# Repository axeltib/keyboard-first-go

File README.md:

# My first keyboard project

## Introduction

## Where to find stuff

# Some good resource

- For generating keboard layouts http://www.keyboard-layout-editor.com/#/
- For generating cad files from layout http://builder.swillkb.com/

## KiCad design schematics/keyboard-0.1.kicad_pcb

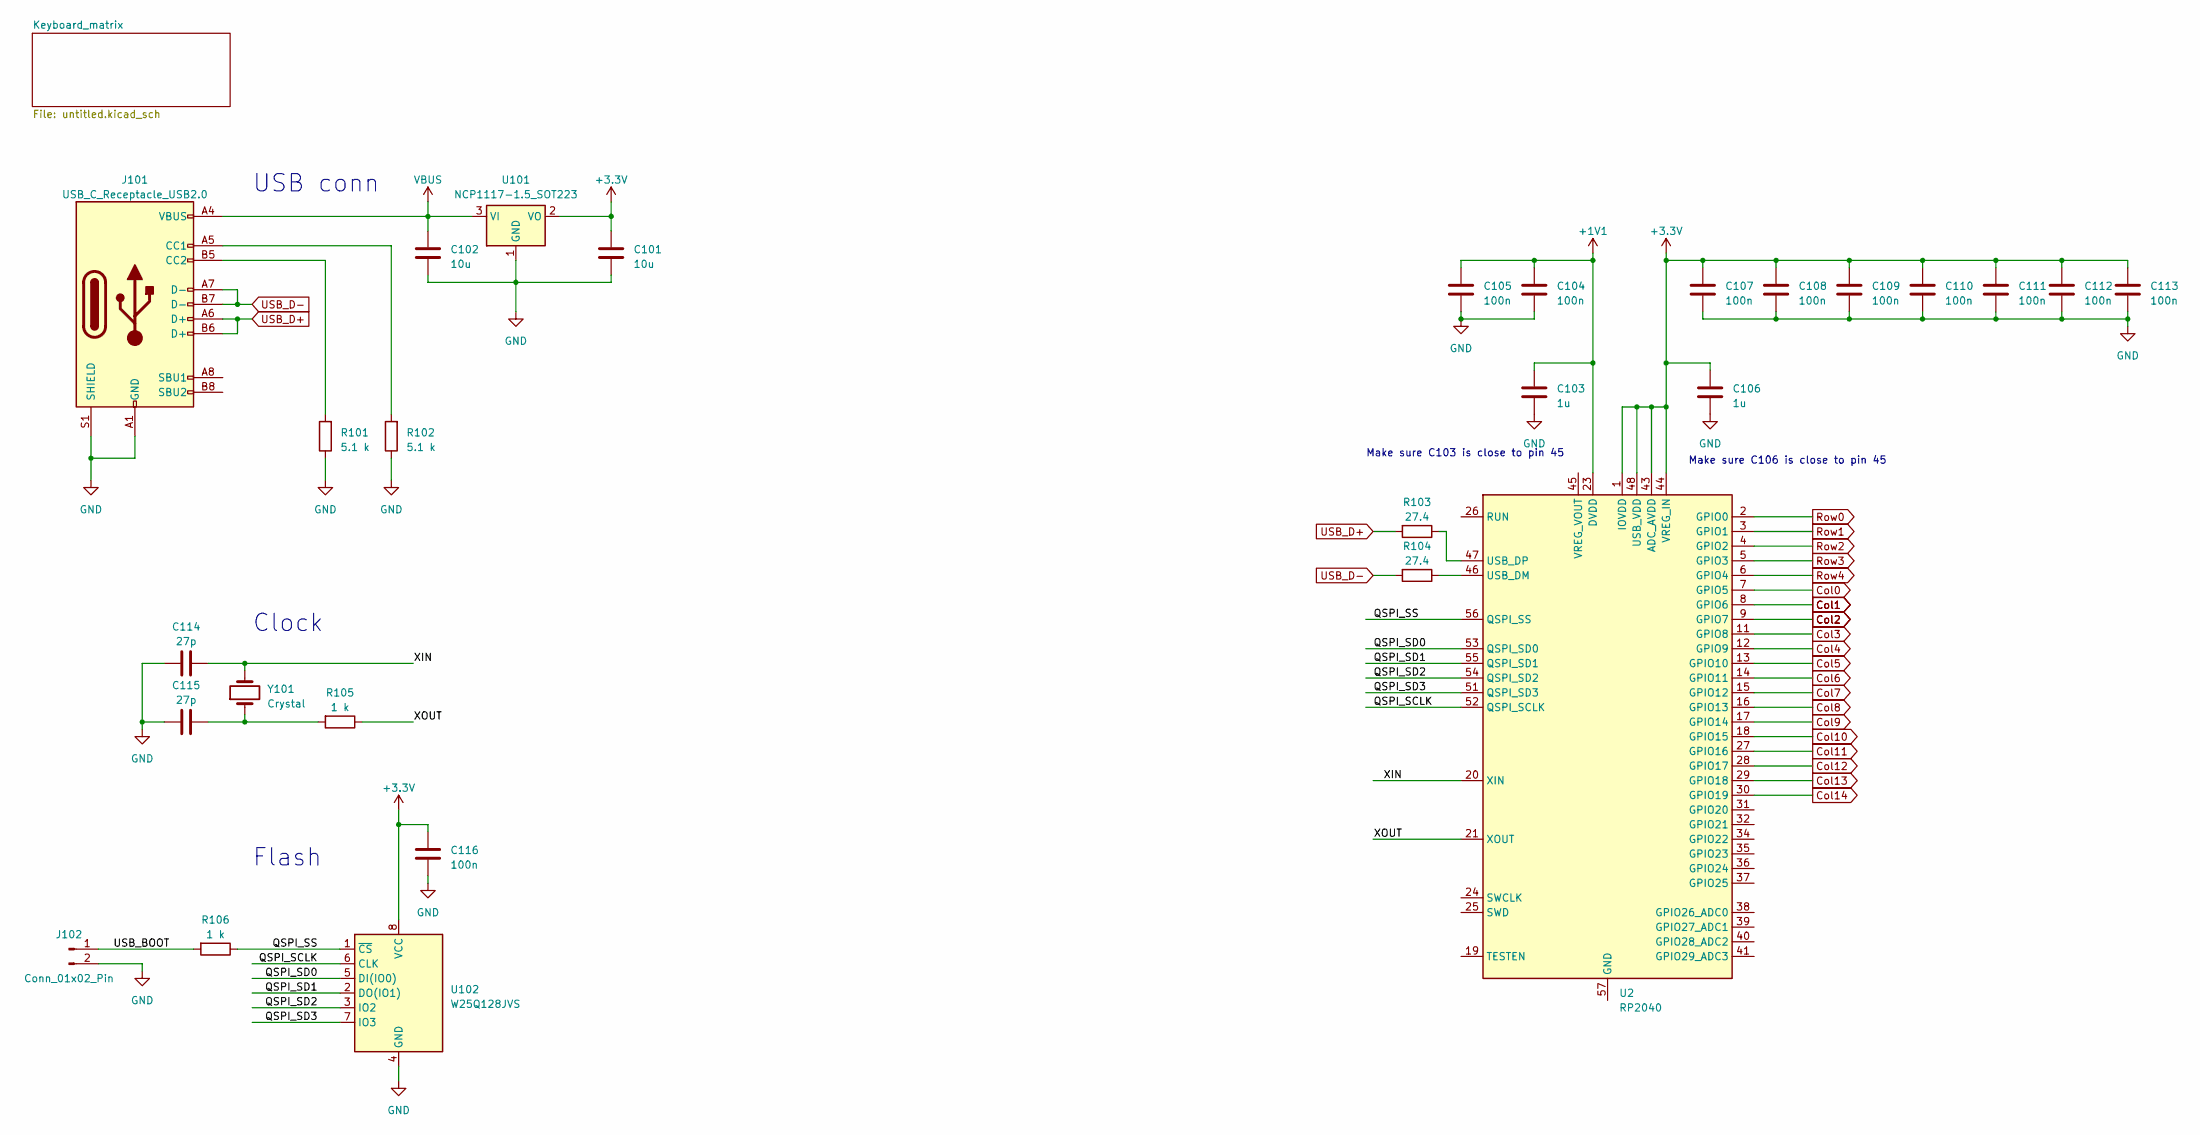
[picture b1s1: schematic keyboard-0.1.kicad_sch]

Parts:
C101, C102: 10u; C_0201_0603Metric
C103, C106: 1u; C_0201_0603Metric
C104, C105, C107, C108, C109, C110, C111, C112, C113, C116: 100n; C_0201_0603Metric
C114, C115: 27p; C_0201_0603Metric
J101: USB_C_Receptacle_USB2.0; USB_C_Receptacle_Amphenol_12401548E4-2A
J102: Conn_01x02_Pin; R_0805_2012Metric_Pad1.20x1.40mm_HandSolder
R101, R102: 5.1 k; R_0201_0603Metric
R103, R104: 27.4; R_0201_0603Metric
R105, R106: 1 k; R_0201_0603Metric
U2: RP2040; QFN-56-1EP_7x7mm_P0.4mm_EP3.2x3.2mm
U101: NCP1117-1.5_SOT223; SOT-223-3_TabPin2
U102: W25Q128JVS; SOIC-8_5.23x5.23mm_P1.27mm
Y101: Crystal; Crystal_SMD_0603-2Pin_6.0x3.5mm

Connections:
+1V1: C103.1, C104.1, C105.1, U2.23 (DVDD), U2.50 (DVDD)
+3.3V: C101.1, C106.1, C107.1, C108.1, C109.1, C110.1, C111.1, C112.1, C113.1, C116.1, U2.1 (IOVDD), U2.10 (IOVDD), U2.22 (IOVDD), U2.33 (IOVDD), U2.42 (IOVDD), U2.43 (ADC_AVDD), U2.44 (VREG_IN), U2.48 (USB_VDD), U2.49 (IOVDD), U101.2 (VO), U102.8 (VCC)
/QSPI_SCLK: U2.52 (QSPI_SCLK), U102.6 (CLK)
/QSPI_SD0: U2.53 (QSPI_SD0), U102.5 (DI(IO0))
/QSPI_SD1: U2.55 (QSPI_SD1), U102.2 (DO(IO1))
/QSPI_SD2: U2.54 (QSPI_SD2), U102.3 (IO2)
/QSPI_SD3: U2.51 (QSPI_SD3), U102.7 (IO3)
/QSPI_SS: R106.1, U2.56 (QSPI_SS), U102.1 (~CS)
/USB_BOOT: J102.1, R106.2
/XIN: C114.2, U2.20 (XIN), Y101.2
/XOUT: R105.1, U2.21 (XOUT)
Col0: U2.7 (GPIO5); also elsewhere on the board
Col1: U2.8 (GPIO6); also elsewhere on the board
Col2: U2.9 (GPIO7); also elsewhere on the board
Col3: U2.11 (GPIO8); also elsewhere on the board
Col4: U2.12 (GPIO9); also elsewhere on the board
Col5: U2.13 (GPIO10); also elsewhere on the board
Col6: U2.14 (GPIO11); also elsewhere on the board
Col7: U2.15 (GPIO12); also elsewhere on the board
Col8: U2.16 (GPIO13); also elsewhere on the board
Col9: U2.17 (GPIO14); also elsewhere on the board
Col10: U2.18 (GPIO15); also elsewhere on the board
Col11: U2.27 (GPIO16); also elsewhere on the board
Col12: U2.28 (GPIO17); also elsewhere on the board
Col13: U2.29 (GPIO18); also elsewhere on the board
Col14: U2.30 (GPIO19)
GND: C101.2, C102.2, C103.2, C104.2, C105.2, C106.2, C107.2, C108.2, C109.2, C110.2, C111.2, C112.2, C113.2, C114.1, C115.1, C116.2, J101.A1 (GND), J101.A12 (GND), J101.B1 (GND), J101.B12 (GND), J101.S1 (SHIELD), J102.2, R101.1, R102.1, U101.1 (GND), U102.4 (GND)
unnamed: C115.2, R105.2, Y101.1
unnamed: J101.A5 (CC1), R102.2
unnamed: J101.B5 (CC2), R101.2
unnamed: R104.1, U2.46 (USB_DM)
unnamed: R103.1, U2.47 (USB_DP)
Row0: U2.2 (GPIO0); also elsewhere on the board
Row1: U2.3 (GPIO1); also elsewhere on the board
Row2: U2.4 (GPIO2); also elsewhere on the board
Row3: U2.5 (GPIO3); also elsewhere on the board
Row4: U2.6 (GPIO4); also elsewhere on the board
USB_D+: J101.A6 (D+), J101.B6 (D+), R103.2
USB_D-: J101.A7 (D-), J101.B7 (D-), R104.2
VBUS: C102.1, J101.A4 (VBUS), J101.A9 (VBUS), J101.B4 (VBUS), J101.B9 (VBUS), U101.3 (VI)

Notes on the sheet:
USB conn
Clock
Make sure C106 is close to pin 45
Flash
Make sure C103 is close to pin 45

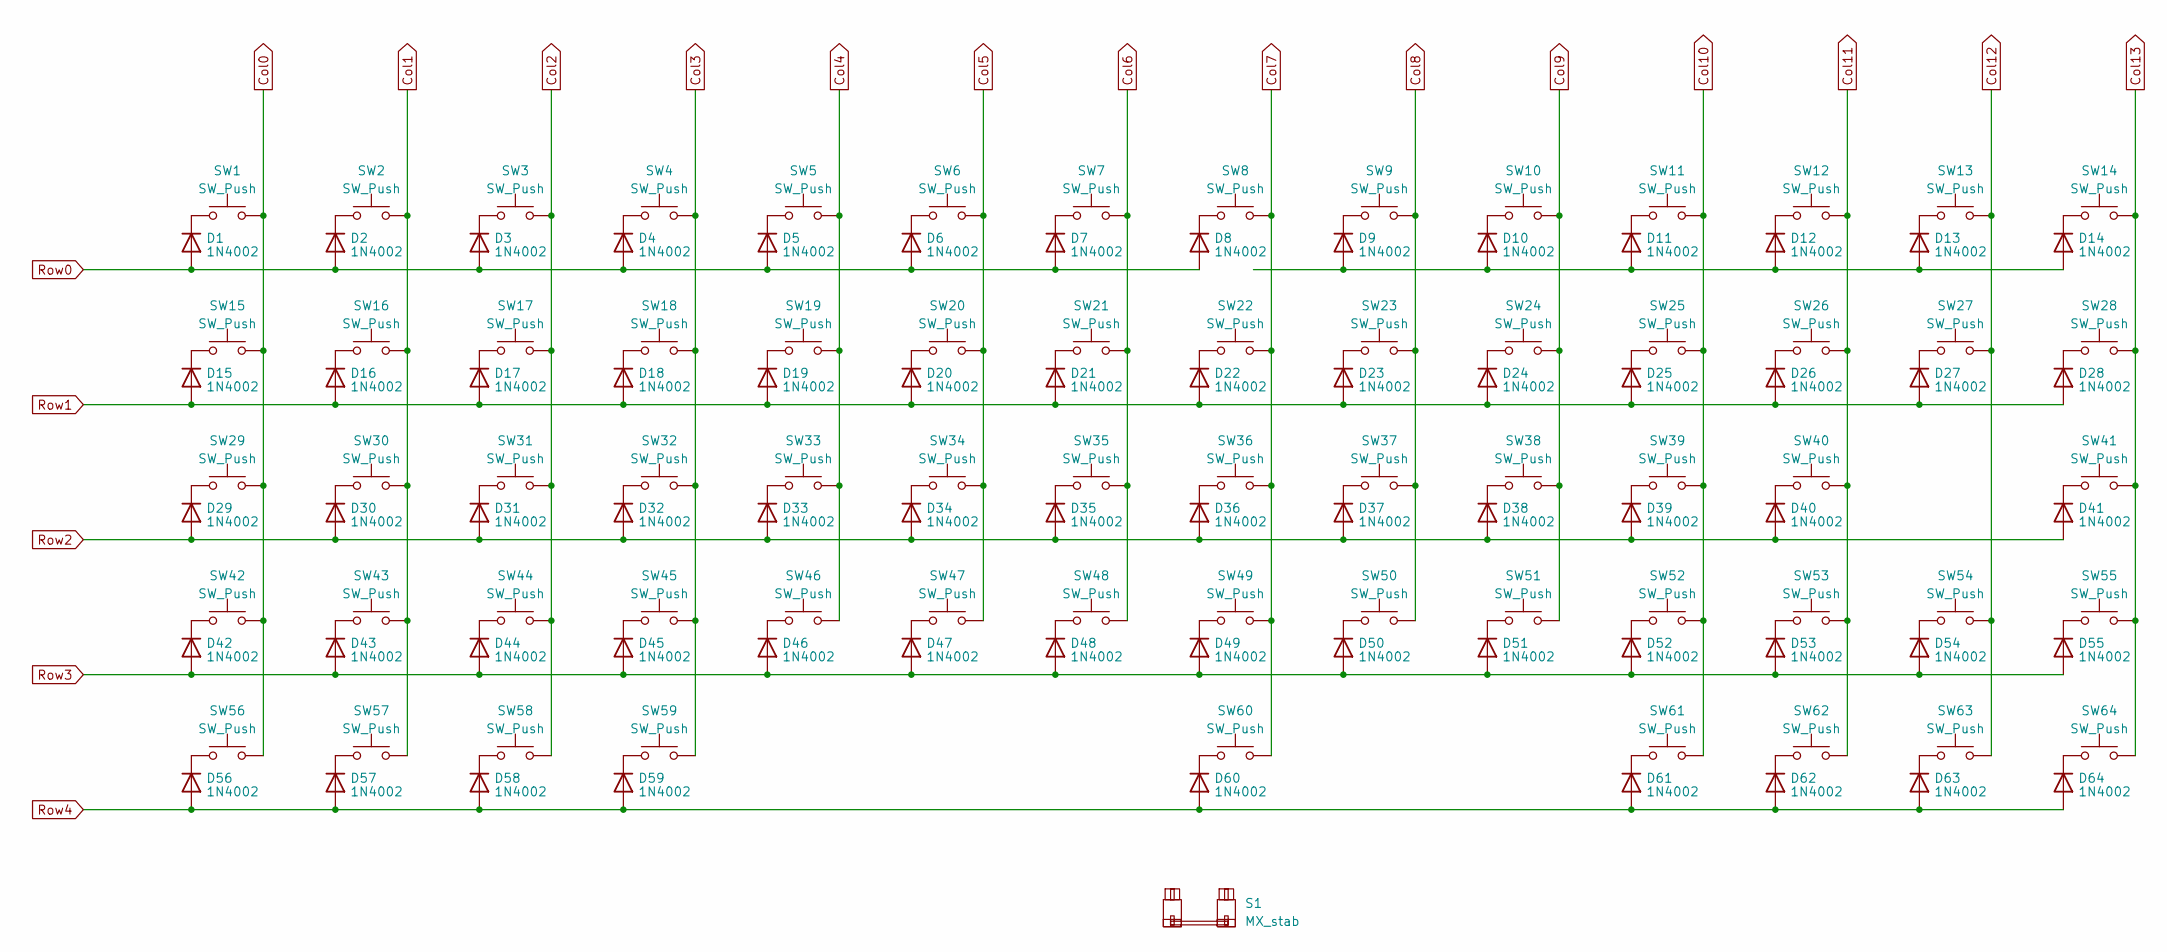
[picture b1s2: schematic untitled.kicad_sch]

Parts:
D1, D2, D3, D4, D5, D6, D7, D8, D9, D10, D11, D12, D13, D14, D15, D16, D17, D18, D19, D20, D21, D22, D23, D24, D25, D26, D27, D28, D29, D30, D31, D32, D33, D34, D35, D36, D37, D38, D39, D40, D41, D42, D43, D44, D45, D46, D47, D48, D49, D50, D51, D52, D53, D54, D55, D56, D57, D58, D59, D60, D61, D62, D63, D64: 1N4002; D_SOD-123
S1: MX_stab; STAB_MX_P_6u
SW1, SW2, SW3, SW4, SW5, SW6, SW7, SW8, SW9, SW10, SW11, SW12, SW13, SW16, SW17, SW18, SW19, SW20, SW21, SW22, SW23, SW24, SW25, SW26, SW27, SW28, SW30, SW31, SW32, SW33, SW34, SW35, SW36, SW37, SW38, SW39, SW40, SW43, SW44, SW45, SW46, SW47, SW48, SW49, SW50, SW51, SW52, SW53, SW54, SW55, SW57, SW58, SW59, SW60, SW62, SW63, SW64: SW_Push; SW_MX_1u
SW14, SW15, SW42: SW_Push; SW_MX_1.5u
SW29, SW41: SW_Push; SW_MX_1.75u
SW56, SW61: SW_Push; SW_MX_1.25u

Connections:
Col0: SW1.2, SW15.2, SW29.2, SW42.2, SW56.2; also elsewhere on the board
Col1: SW2.2, SW16.2, SW30.2, SW43.2, SW57.2; also elsewhere on the board
Col2: SW3.2, SW17.2, SW31.2, SW44.2, SW58.2; also elsewhere on the board
Col3: SW4.2, SW18.2, SW32.2, SW45.2, SW59.2; also elsewhere on the board
Col4: SW5.2, SW19.2, SW33.2, SW46.2; also elsewhere on the board
Col5: SW6.2, SW20.2, SW34.2, SW47.2; also elsewhere on the board
Col6: SW7.2, SW21.2, SW35.2, SW48.2; also elsewhere on the board
Col7: SW8.2, SW22.2, SW36.2, SW49.2, SW60.2; also elsewhere on the board
Col8: SW9.2, SW23.2, SW37.2, SW50.2; also elsewhere on the board
Col9: SW10.2, SW24.2, SW38.2, SW51.2; also elsewhere on the board
Col10: SW11.2, SW25.2, SW39.2, SW52.2, SW61.2; also elsewhere on the board
Col11: SW12.2, SW26.2, SW40.2, SW53.2, SW62.2; also elsewhere on the board
Col12: SW13.2, SW27.2, SW54.2, SW63.2; also elsewhere on the board
Col13: SW14.2, SW28.2, SW41.2, SW55.2, SW64.2; also elsewhere on the board
unnamed: D1.1 (K), SW1.1
unnamed: D2.1 (K), SW2.1
unnamed: D3.1 (K), SW3.1
unnamed: D4.1 (K), SW4.1
unnamed: D5.1 (K), SW5.1
unnamed: D6.1 (K), SW6.1
unnamed: D7.1 (K), SW7.1
unnamed: D8.1 (K), SW8.1
unnamed: D9.1 (K), SW9.1
unnamed: D9.2 (A), D10.2 (A), D11.2 (A), D12.2 (A), D13.2 (A), D14.2 (A)
unnamed: D10.1 (K), SW10.1
unnamed: D11.1 (K), SW11.1
unnamed: D12.1 (K), SW12.1
unnamed: D13.1 (K), SW13.1
unnamed: D14.1 (K), SW14.1
unnamed: D15.1 (K), SW15.1
unnamed: D16.1 (K), SW16.1
unnamed: D17.1 (K), SW17.1
unnamed: D18.1 (K), SW18.1
unnamed: D19.1 (K), SW19.1
unnamed: D20.1 (K), SW20.1
unnamed: D21.1 (K), SW21.1
unnamed: D22.1 (K), SW22.1
unnamed: D23.1 (K), SW23.1
unnamed: D24.1 (K), SW24.1
unnamed: D25.1 (K), SW25.1
unnamed: D26.1 (K), SW26.1
unnamed: D27.1 (K), SW27.1
unnamed: D28.1 (K), SW28.1
unnamed: D29.1 (K), SW29.1
unnamed: D30.1 (K), SW30.1
unnamed: D31.1 (K), SW31.1
unnamed: D32.1 (K), SW32.1
unnamed: D33.1 (K), SW33.1
unnamed: D34.1 (K), SW34.1
unnamed: D35.1 (K), SW35.1
unnamed: D36.1 (K), SW36.1
unnamed: D37.1 (K), SW37.1
unnamed: D38.1 (K), SW38.1
unnamed: D39.1 (K), SW39.1
unnamed 68: D40.1 (K), SW40.1; also elsewhere on the board
unnamed: D41.1 (K), SW41.1
unnamed: D42.1 (K), SW42.1
unnamed: D43.1 (K), SW43.1
unnamed: D44.1 (K), SW44.1
unnamed: D45.1 (K), SW45.1
unnamed: D46.1 (K), SW46.1
unnamed: D47.1 (K), SW47.1
unnamed: D48.1 (K), SW48.1
unnamed: D49.1 (K), SW49.1
unnamed: D50.1 (K), SW50.1
unnamed: D51.1 (K), SW51.1
unnamed: D52.1 (K), SW52.1
unnamed: D53.1 (K), SW53.1
unnamed: D54.1 (K), SW54.1
unnamed: D55.1 (K), SW55.1
unnamed: D56.1 (K), SW56.1
unnamed: D57.1 (K), SW57.1
unnamed: D58.1 (K), SW58.1
unnamed: D59.1 (K), SW59.1
unnamed: D60.1 (K), SW60.1
unnamed: D61.1 (K), SW61.1
unnamed: D62.1 (K), SW62.1
unnamed: D63.1 (K), SW63.1
unnamed: D64.1 (K), SW64.1
Row0: D1.2 (A), D2.2 (A), D3.2 (A), D4.2 (A), D5.2 (A), D6.2 (A), D7.2 (A), D8.2 (A); also elsewhere on the board
Row1: D15.2 (A), D16.2 (A), D17.2 (A), D18.2 (A), D19.2 (A), D20.2 (A), D21.2 (A), D22.2 (A), D23.2 (A), D24.2 (A), D25.2 (A), D26.2 (A), D27.2 (A), D28.2 (A); also elsewhere on the board
Row2: D29.2 (A), D30.2 (A), D31.2 (A), D32.2 (A), D33.2 (A), D34.2 (A), D35.2 (A), D36.2 (A), D37.2 (A), D38.2 (A), D39.2 (A), D40.2 (A), D41.2 (A); also elsewhere on the board
Row3: D42.2 (A), D43.2 (A), D44.2 (A), D45.2 (A), D46.2 (A), D47.2 (A), D48.2 (A), D49.2 (A), D50.2 (A), D51.2 (A), D52.2 (A), D53.2 (A), D54.2 (A), D55.2 (A); also elsewhere on the board
Row4: D56.2 (A), D57.2 (A), D58.2 (A), D59.2 (A), D60.2 (A), D61.2 (A), D62.2 (A), D63.2 (A), D64.2 (A); also elsewhere on the board

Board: 2 copper layers, 158 parts (0 on the bottom side), 104 nets, no tracks yet.

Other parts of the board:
D40#2: 1N4002; D_0201_0603Metric

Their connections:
unnamed 68: D40#2.1 (K); also elsewhere on the board
Row2: D40#2.2 (A); also elsewhere on the board

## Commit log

2023-07-08 (chore) move files
2023-07-08 (feat) add power flash usb and clock to sch
2023-07-09 (feat) first layout
